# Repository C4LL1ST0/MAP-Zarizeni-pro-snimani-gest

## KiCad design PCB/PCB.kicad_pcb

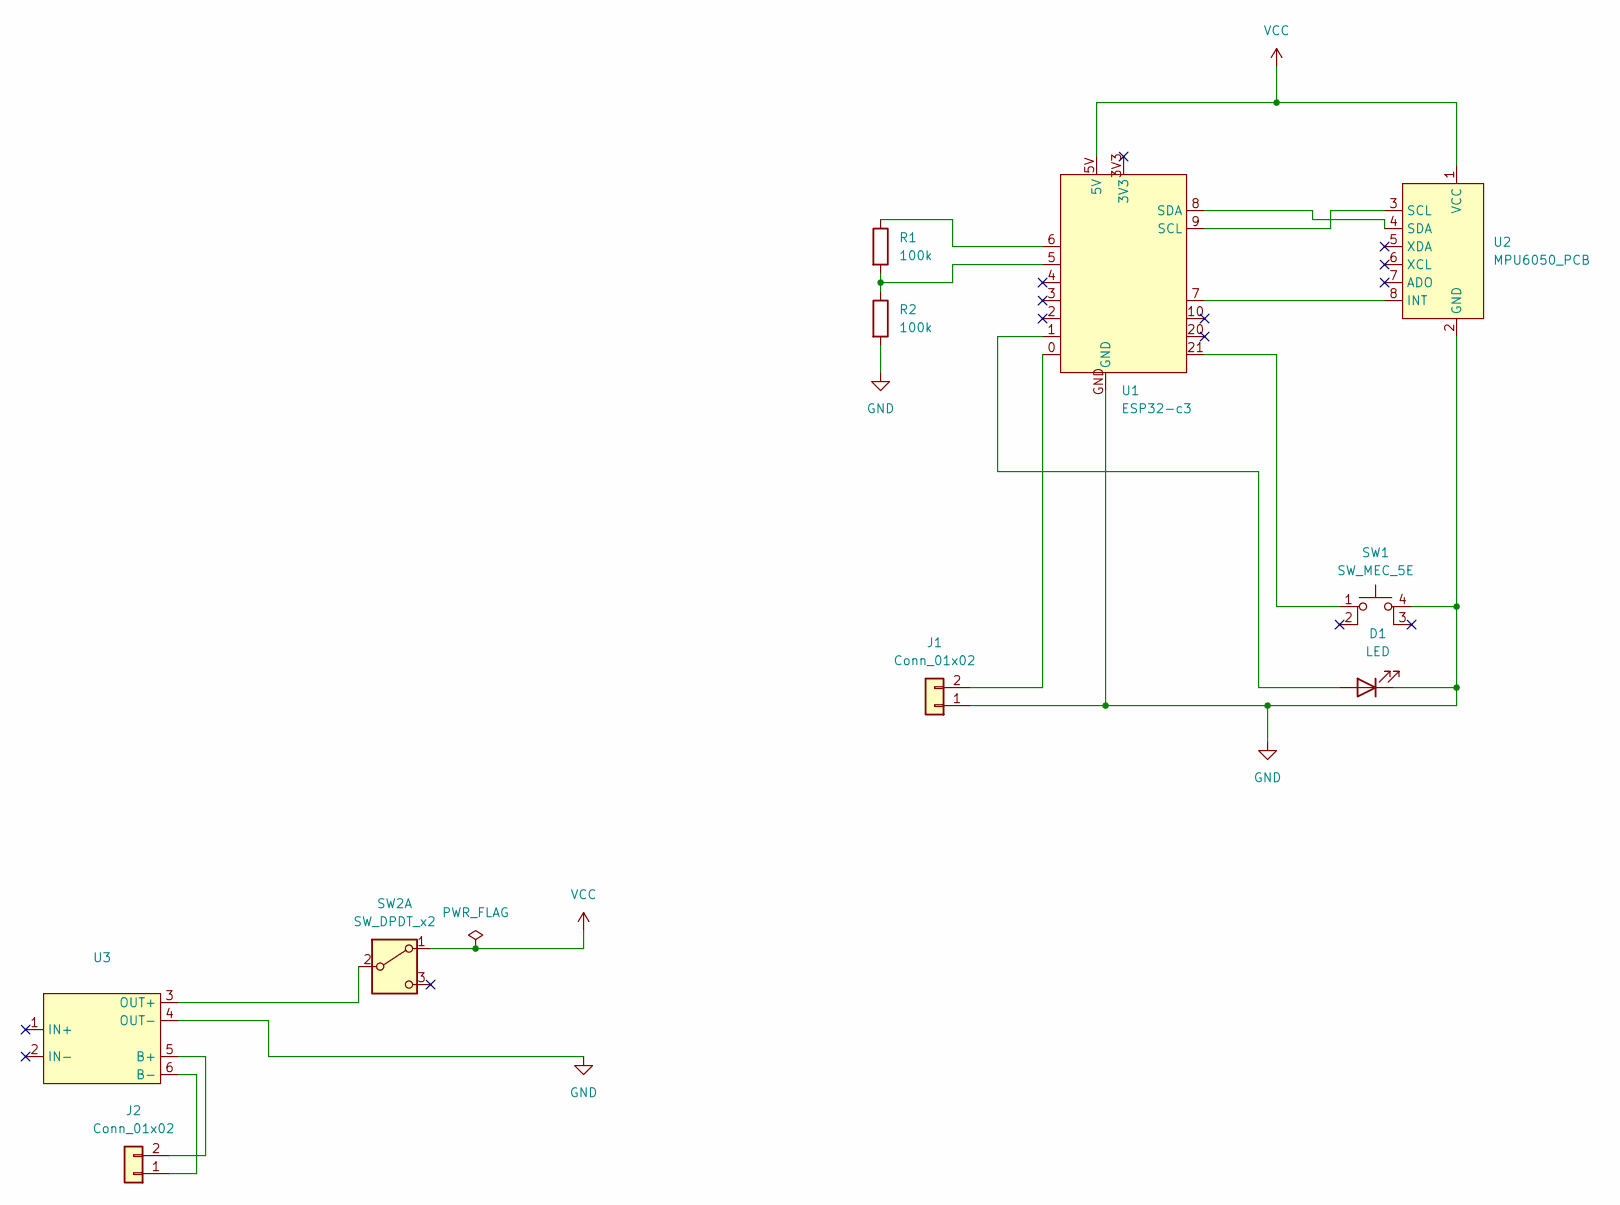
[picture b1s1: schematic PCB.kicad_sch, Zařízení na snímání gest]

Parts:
D1: LED; LED_Oval_W5.2mm_H3.8mm
J1, J2: Conn_01x02; conn_2p_THT_moje
R1, R2: 100k; R_Axial_DIN0207_L6.3mm_D2.5mm_P7.62mm_Horizontal
SW1: SW_MEC_5E; Arduino_tlacitko
SW2: SW_DPDT_x2; KLS_on_on_moje
U1: ESP32-c3; ESP32-C3-SUPERMINI
U2: MPU6050_PCB; MPU6050_PCB_moje
U3: TP4056

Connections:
GND: D1.1 (K), J1.1, R2.2, SW1.4 (A), U1.GND, U2.2 (GND), U3.4 (OUT-)
unnamed: D1.2 (A), U1.1
unnamed: J1.2, U1.0
unnamed: J2.1, U3.6 (B-)
unnamed: J2.2, U3.5 (B+)
unnamed: R1.1, U1.6
unnamed: R1.2, R2.1, U1.5
unnamed: SW1.1, U1.21
unnamed: SW2.2 (B), U3.3 (OUT+)
unnamed: U1.9 (SCL), U2.3 (SCL)
unnamed: U1.8 (SDA), U2.4 (SDA)
unnamed: U1.7, U2.8 (INT)
VCC: SW2.1 (A), U1.5V, U2.1 (VCC)

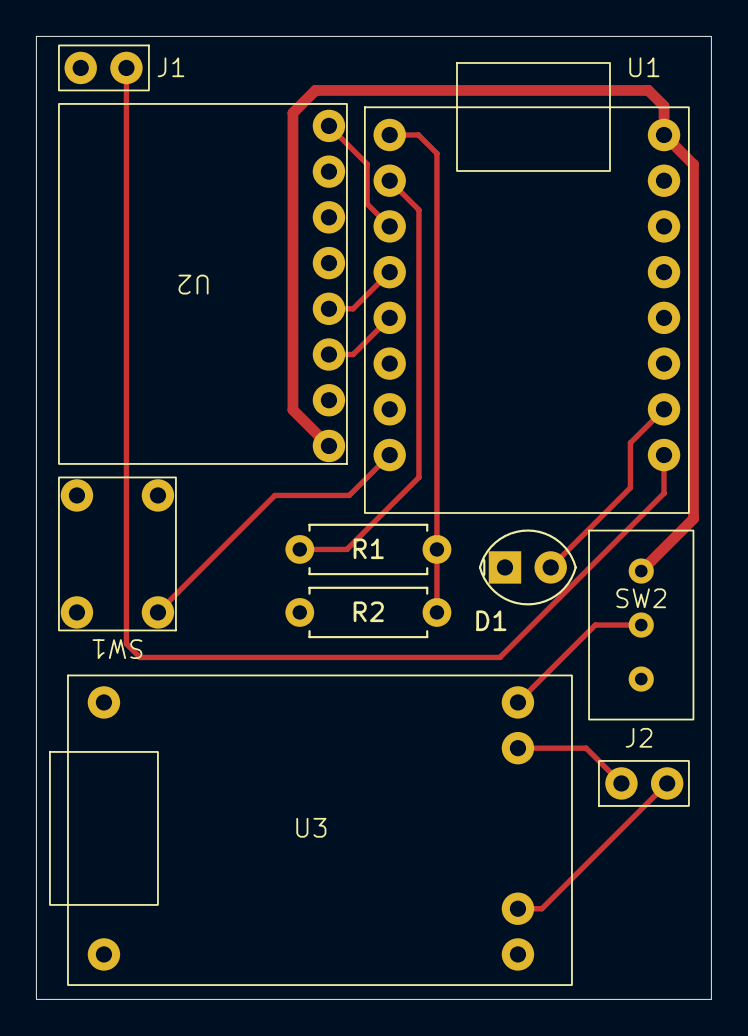
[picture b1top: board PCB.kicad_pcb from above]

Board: 2 copper layers, 37.5 x 53.5 mm, 10 parts (0 on the bottom side), 13 nets.

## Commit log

2025-09-15 feat: harmonogram
2025-09-30 feat: mockdata
2025-11-22 feat: driver proj created
2025-11-22 feat: readme updated
2025-11-22 fix: add gitignore
2025-11-22 fix: add gitignore 2
2025-11-22 fix: add gitignore 3
2025-11-22 fix: gitignore
2025-11-22 fix: del cache folder§
2025-11-22 feat: receiving and caching sensor values
2025-11-23 feat: collecting training data - WIP
2025-11-25 feat: training data collection functional
2025-12-08 feat: 3D-models added
2025-12-08 feat: version 4
2025-12-08 feat: vystup 1 uploaded
2025-12-08 feat: template added
2025-12-09 fix: rebase
2025-12-10 feat: add firmware
2025-12-10 fix: vystup2 moved
2025-12-13 feat: vystup2_v1 Bilek
2025-12-13 feat: hodiny updated
2025-12-14 fix: vystup 2 optim
2025-12-16 feat: added newest MAP-krabicka
2025-12-17 fix: unpacking none
2026-01-03 feat: padding and loop added
2026-01-08 feat: left + right added
2026-01-09 fix: clear cache after each geture
2026-01-10 feat: train, save, load model maybe functional
2026-01-11 feat: licence
2026-01-11 fix: AIService accually might work
2026-01-12 refactor: main/receiving training data, feat: Cache thread safe
2026-01-15 feat: UI propably usable for normal usage
2026-01-15 feat: ui refactor, keyboard shortcuts, TODO: make train data collecting run in other thread
2026-01-23 feat:frequency and gesture length changed. Added padding and croping
2026-01-23 feat: changed firmware
2026-01-23 feat: Recieving data in UI
2026-01-24 feat: first model trained. Gesture evaluation to be tested.
2026-01-25 feat: vystup 3
2026-01-26 fix: norm=none
2026-01-26 feat: model retrained
2026-01-27 feat: Now it works ig
2026-01-27 fix: goofy ahh branching when gesture none or not complete
2026-01-27 fix: everything (model predictions)
2026-01-27 feat: model functional
2026-01-27 feat: PptControler created
2026-01-27 feat: vystupy and table of hours added
2026-01-27 refactor: code cleaned up and modely organized
2026-01-28 fix: use conda packages
2026-02-01 feat: train data cropper
2026-02-02 feat: gesture length set to 38
2026-02-06 feat: firmware optimized, gesture lenght 45
2026-02-07 feat: vystup 4 - ja
2026-02-10 fix:PptControler fixed
2026-02-10 updt: updated ignore
2026-02-10 feat: deleted gcode
2026-02-10 fix: imports
2026-02-22 feat: zaverecna zprava, pcb m2 WIP
2026-03-03 feat: ZZ, model retrained
2026-03-03 fix: eeeeh cache
2026-03-03 fix: timiout after gesture evaluation
2026-03-03 fix: timiout after gesture evaluation part 2
2026-03-24 feat: idk
2026-04-07 feat: updated git ignore
2026-04-07 feat: pcb model 2 gerbers
2026-04-14 fix: readable pc_driver readme
2026-04-14 feat: updated readme (todos)
2026-04-21 feat: thumb button
2026-04-21 feat: UP, DOWN gesture WIP
2026-04-22 fix: ppt controller works on linux
2026-04-22 fix: choose newest model available
2026-04-24 feat: UP/DOWN GESTURES work, training counter
